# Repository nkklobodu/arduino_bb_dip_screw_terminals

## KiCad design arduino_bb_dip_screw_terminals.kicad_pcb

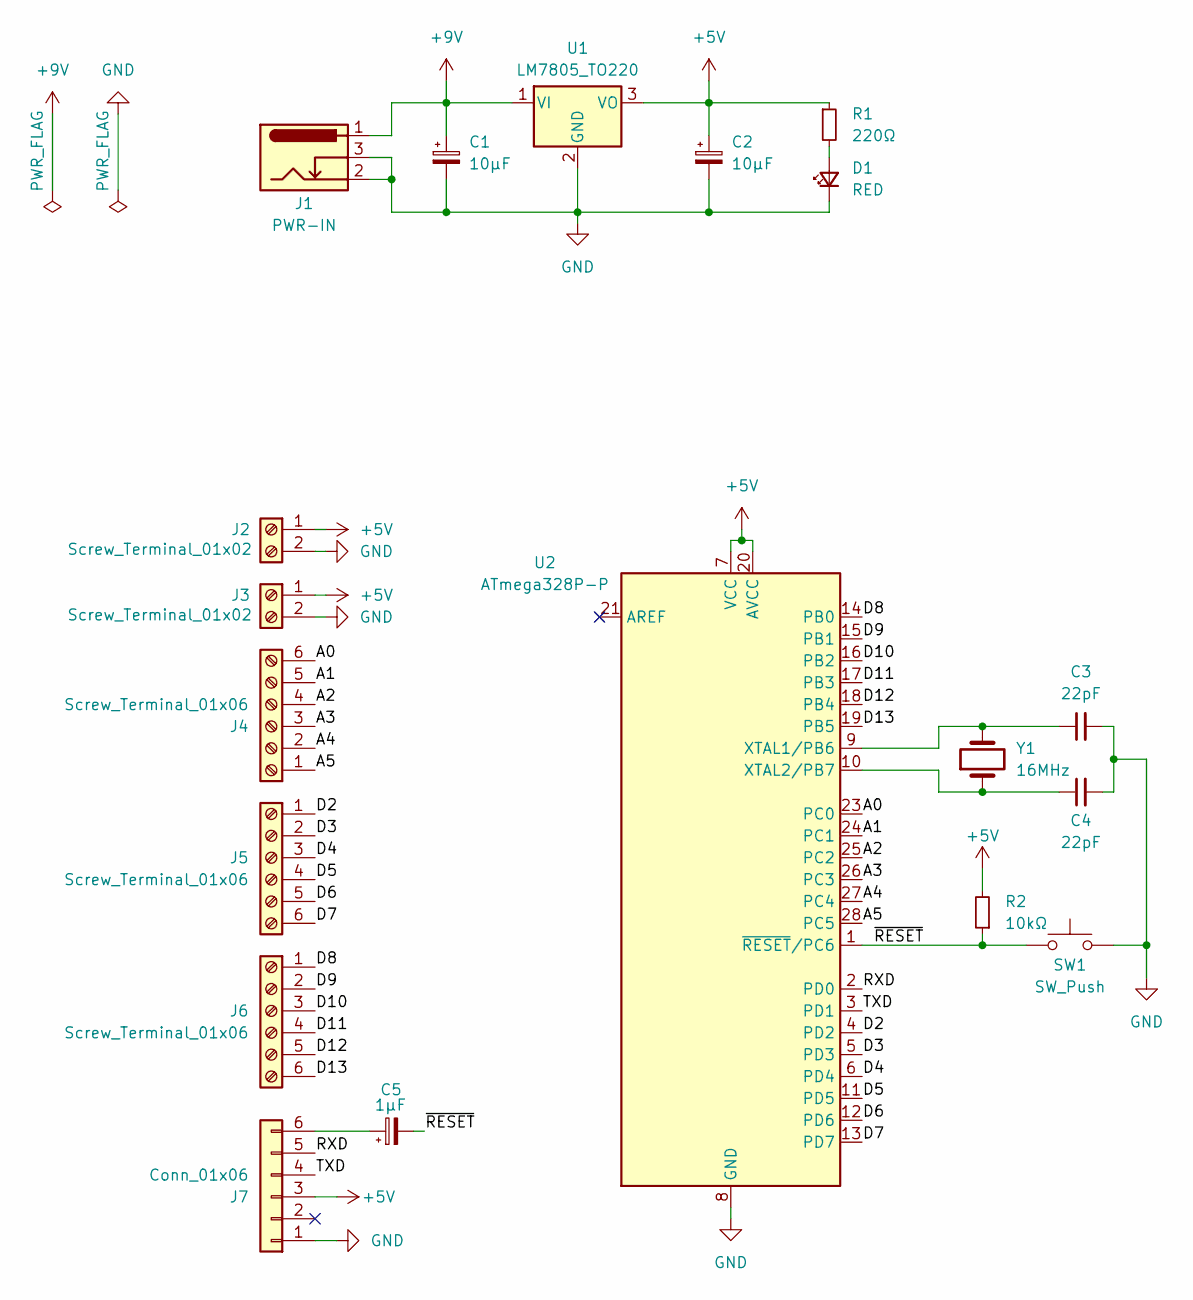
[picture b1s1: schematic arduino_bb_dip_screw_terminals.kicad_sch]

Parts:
C1, C2: 10µF; CP_Radial_D8.0mm_P2.50mm
C3, C4: 22pF; C_Disc_D6.0mm_W4.4mm_P5.00mm
C5: 1µF; CP_Radial_D5.0mm_P2.50mm
D1: RED; LED_D3.0mm
J1: PWR-IN; BarrelJack_Horizontal
J2, J3: Screw_Terminal_01x02; TerminalBlock_Phoenix_MKDS-1,5-2_1x02_P5.00mm_Horizontal
J4, J5, J6: Screw_Terminal_01x06; TerminalBlock_Phoenix_MKDS-1,5-6_1x06_P5.00mm_Horizontal
J7: Conn_01x06; PinSocket_1x06_P2.00mm_Vertical
R1: 220Ω; R_Axial_DIN0207_L6.3mm_D2.5mm_P10.16mm_Horizontal
R2: 10kΩ; R_Axial_DIN0207_L6.3mm_D2.5mm_P10.16mm_Horizontal
SW1: SW_Push; SW_PUSH_6mm_H4.3mm
U1: LM7805_TO220; TO-220-3_Vertical
U2: ATmega328P-P; DIP-28_W7.62mm
Y1: 16MHz; Crystal_HC49-4H_Vertical

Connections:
+5V: C2.1, J2.1, J3.1, J7.3, R1.1, R2.2, U1.3 (VO), U2.7 (VCC), U2.20 (AVCC)
+9V: C1.1, J1.1, U1.1 (VI)
/A0: J4.6, U2.23 (PC0)
/A1: J4.5, U2.24 (PC1)
/A2: J4.4, U2.25 (PC2)
/A3: J4.3, U2.26 (PC3)
/A4: J4.2, U2.27 (PC4)
/A5: J4.1, U2.28 (PC5)
/D2: J5.1, U2.4 (PD2)
/D3: J5.2, U2.5 (PD3)
/D4: J5.3, U2.6 (PD4)
/D5: J5.4, U2.11 (PD5)
/D6: J5.5, U2.12 (PD6)
/D7: J5.6, U2.13 (PD7)
/D8: J6.1, U2.14 (PB0)
/D9: J6.2, U2.15 (PB1)
/D10: J6.3, U2.16 (PB2)
/D11: J6.4, U2.17 (PB3)
/D12: J6.5, U2.18 (PB4)
/D13: J6.6, U2.19 (PB5)
/RXD: J7.5, U2.2 (PD0)
/TXD: J7.4, U2.3 (PD1)
/~RESET: C5.2, R2.1, SW1.1, U2.1 (~RESET/PC6)
GND: C1.2, C2.2, C3.2, C4.2, D1.1 (K), J1.2, J1.3, J2.2, J3.2, J7.1, SW1.2, U1.2 (GND), U2.8 (GND), U2.22 (GND)
unnamed: D1.2 (A), R1.2
unnamed: C5.1, J7.6
unnamed: C3.1, U2.9 (XTAL1/PB6), Y1.2
unnamed: C4.1, U2.10 (XTAL2/PB7), Y1.1

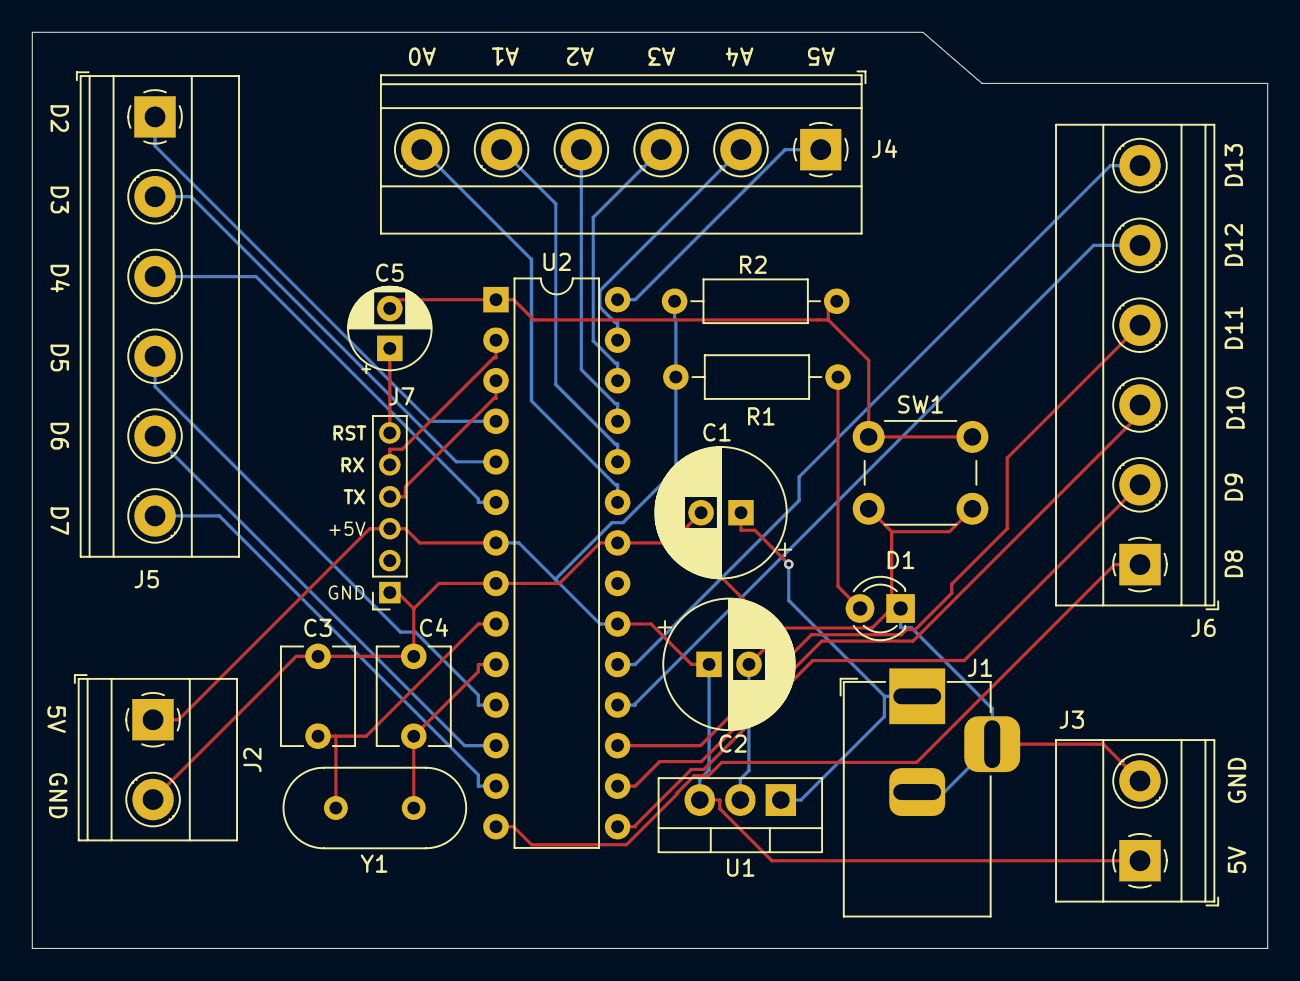
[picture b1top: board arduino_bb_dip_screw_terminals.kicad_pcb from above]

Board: 2 copper layers, 77.4 x 57.4 mm, 19 parts (0 on the bottom side), 28 nets.

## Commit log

2024-05-27 updated .gitignore
